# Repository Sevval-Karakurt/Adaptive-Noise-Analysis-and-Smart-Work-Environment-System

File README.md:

# Adaptive-Noise-Analysis-and-Smart-Work-Environment-System
​Real-time noise analysis and smart workspace monitoring system featuring MSP430, MAX9814, and HC-05 Bluetooth.

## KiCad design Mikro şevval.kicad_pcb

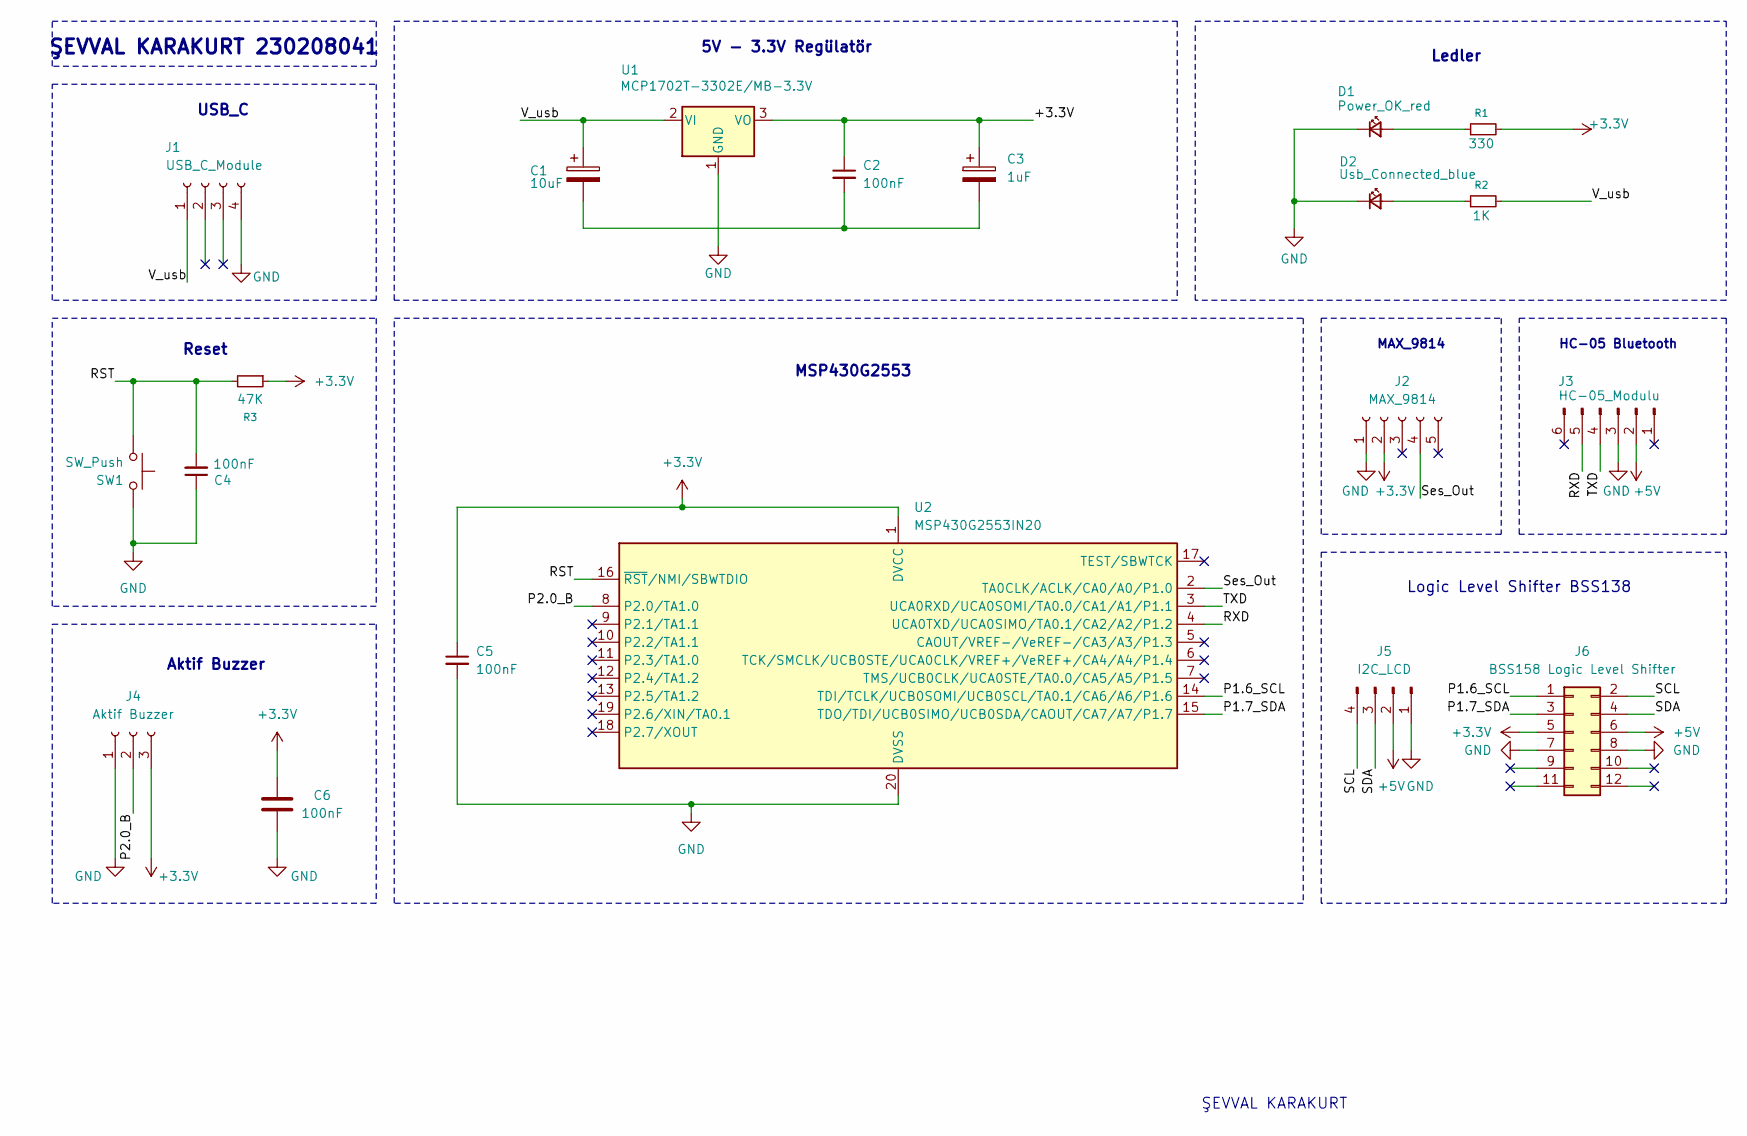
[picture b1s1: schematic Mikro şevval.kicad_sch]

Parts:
C1: 10uF; CP_Radial_D5.0mm_P2.00mm
C2, C4, C5, C6: 100nF; C_Rect_L7.2mm_W2.5mm_P5.00mm_FKS2_FKP2_MKS2_MKP2
C3: 1uF; CP_Radial_D5.0mm_P2.00mm
D1: Power_OK_red; LED_D3.0mm
D2: Usb_Connected_blue; LED_D3.0mm
J1: USB_C_Module; PinSocket_1x04_P2.54mm_Vertical
J2: MAX_9814; PinSocket_1x05_P2.54mm_Vertical
J3: HC-05_Modulu; PinSocket_1x06_P2.54mm_Vertical
J4: Aktif Buzzer; PinSocket_1x03_P2.54mm_Vertical
J5: I2C_LCD; PinSocket_1x04_P2.54mm_Vertical
J6: BSS158 Logic Level Shifter; PinSocket_2x06_P2.54mm_Vertical
R1: 330; R_Axial_DIN0207_L6.3mm_D2.5mm_P7.62mm_Horizontal
R2: 1K; R_Axial_DIN0207_L6.3mm_D2.5mm_P7.62mm_Horizontal
R3: 47K; R_Axial_DIN0207_L6.3mm_D2.5mm_P7.62mm_Horizontal
SW1: SW_Push; SW_PUSH_6mm
U1: MCP1702T-3302E/MB-3.3V; SOT-89-3
U2: MSP430G2553IN20; DIP-20_W7.62mm

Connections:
+3.3V: C2.1, C3.1, C5.1, C6.2, J2.2, J4.3, J6.5, R1.2, R3.1, U1.3 (VO), U2.1 (DVCC)
+5V: J3.2, J5.2, J6.6
/P1.6_SCL: J6.1, U2.14 (TDI/TCLK/UCB0SOMI/UCB0SCL/TA0.1/CA6/A6/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)
/P1.7_SDA: J6.3, U2.15 (TDO/TDI/UCB0SIMO/UCB0SDA/CAOUT/CA7/A7/P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)
/P2.0_B: J4.2, U2.8 (P2.0/TA1.0)
/RST: C4.2, R3.2, SW1.1, U2.16 (~RST/NMI/SBWTDIO)
/RXD: J3.5, U2.4 (UCA0TXD/UCA0SIMO/TA0.1/CA2/A2/P1.2)
/SCL: J5.4, J6.2
/SDA: J5.3, J6.4
/Ses_Out: J2.4, U2.2 (TA0CLK/ACLK/CA0/A0/P1.0)
/TXD: J3.4, U2.3 (UCA0RXD/UCA0SOMI/TA0.0/CA1/A1/P1.1)
/V_usb: C1.1, J1.1, R2.2, U1.2 (VI)
GND: C4.1, C5.2, C6.1, D1.1 (K), D2.1 (K), J1.4, J2.1, J3.3, J4.1, J5.1, J6.7, J6.8, SW1.2, U1.1 (GND), U2.20 (DVSS)
unnamed: C1.2, C2.2, C3.2
unnamed: D1.2 (A), R1.1
unnamed: D2.2 (A), R2.1

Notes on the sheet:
HC-05 Bluetooth
5V - 3.3V Regülatör
Logic Level Shifter BSS138
Aktif Buzzer
ŞEVVAL KARAKURT 230208041
Ledler
MSP430G2553
Reset
MAX_9814
ŞEVVAL KARAKURT
USB_C

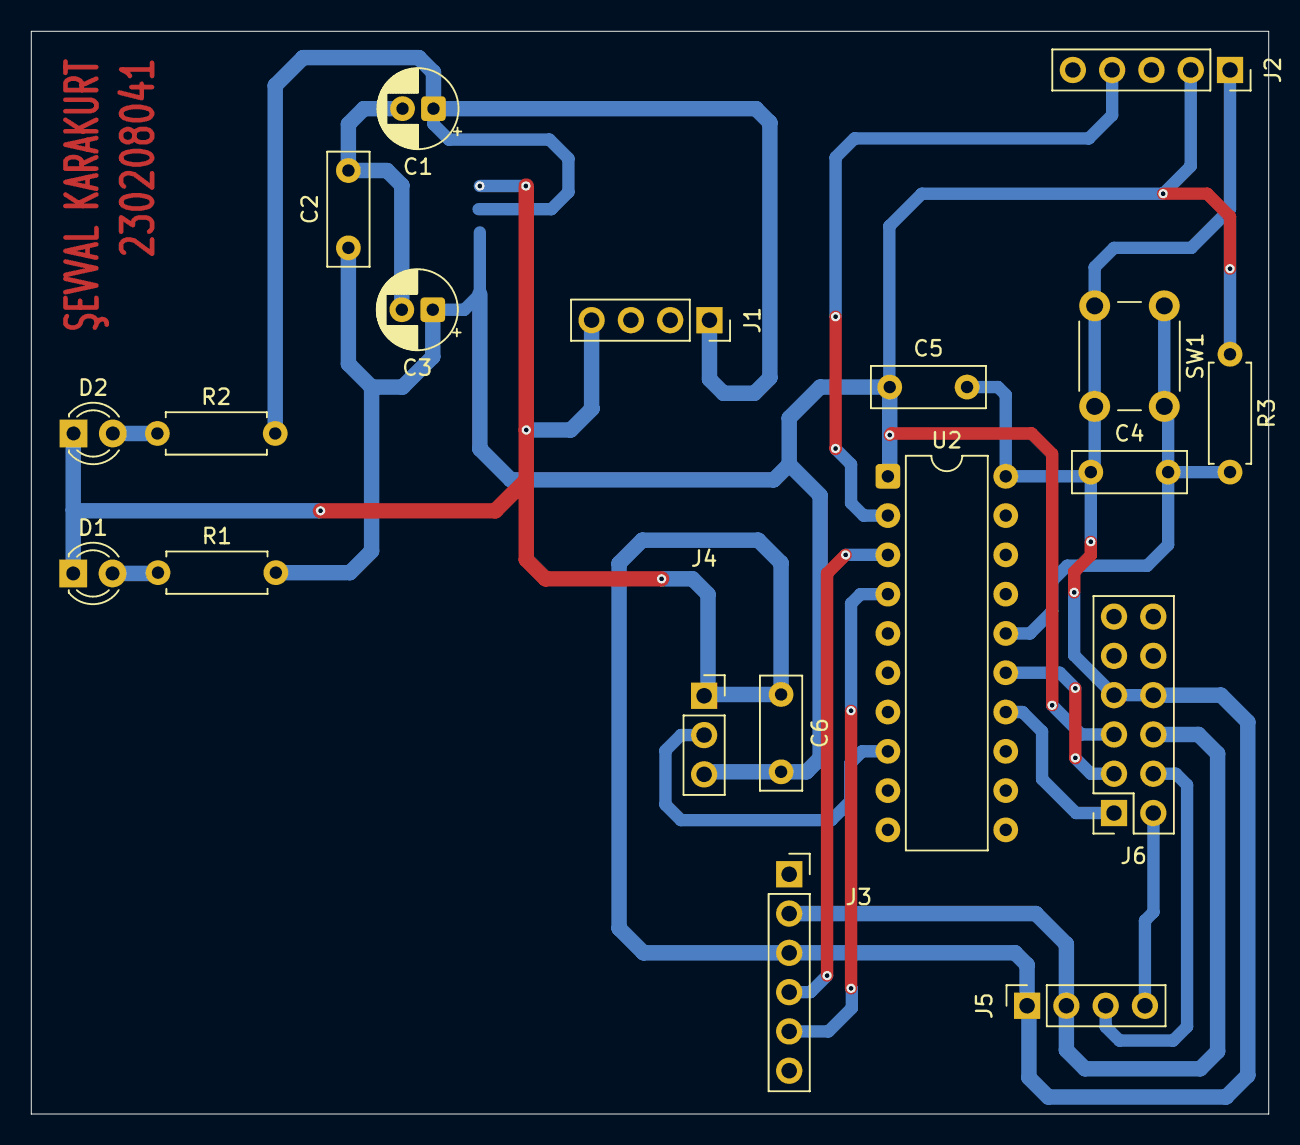
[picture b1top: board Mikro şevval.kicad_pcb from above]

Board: 2 copper layers, 80.0 x 70.0 mm, 20 parts (1 on the bottom side), 16 nets.
